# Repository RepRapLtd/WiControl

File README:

Wireless Home/Building Control System
=====================================

Adrian Bowyer
RepRap Ltd
https://reprapltd.com

Licence: GPL

This is a system for controlling devices in buildings (primarily, but not exclusively, heating; it will also do lighting and other things) with a web interface.  It is fully open-source and free.  The licence is the GPL.

There are two versions:

  1. Raspberry Pi + PanStamp in the directory PanStamp. This has been working for a few years, and is now frozen and will not be developed further.

  2. WiFi based on the ESP-8266 in the directory ESP-8266.  This is in development.

Both start with a php script that serves web pages where you can edit, for example, temperature profiles for individual rooms.  That data is saved in files on the server.

The ESP-8266s (or Pi) then get that data and decide(s) what to turn on and off.

More documentation needs to be written...

More importantly, security is minimal and needs to be properly implemented.

See also (for homemade solenoid valves): https://www.thingiverse.com/thing:3496770

WiControl - ESP-8266
====================

This version does everything that the PanStamp version did, but more simply and robustly (the robustness has nothing to do with the hardware change; the PanStamps are fine; it has to do with a simplification of the protocols and hardware).

This version of the system will also support Google Home and Amazon Echo/Alexa.

Some more instructions here would be a good idea...

WiControl - Raspberry Pi + PanStamp
===================================

This allows temperature profiles to be set for each individual room for all times of the day and every day of the week.

It can be controlled using a web browser from anywhere.

It uses Panstamps (http://www.panstamp.com/) for the individual rooms and a Raspberry Pi (https://www.raspberrypi.org/) as the main building controller.

This repository contains all the software and all the hardware designs.

One thing it lacks is full documentation, as I created it for my own use and I know how it works.  Sorry.

Installation:
-------------

On the Pi:

This assumes you have an out-of-the-box Raspberry Pi SD card with no extra software installed.

First set your local timezone:

$ sudo dpkg-reconfigure tzdata

You may want to change the default name of the Pi ("raspberrypi") to something more appropriate 
like "heatingcontrol".  To do that:

$ sudo nano /etc/hostname

That file contains a single name - the name of the Pi.  Change it to what you want, save the file, then reboot.

Change you password:

$ passwd

And enable ssh:

$ sudo raspi-config

Next install Apache and PHP:

$ sudo apt-get update
$ sudo apt-get install apache2 -y
$ sudo apt-get install php5 libapache2-mod-php5 -y

At this point it is a good idea to check that the webserver is now running.  In the URL address bar of a web browser on a PC or phone type

  myname.home/

where myname is the Pi's name that you created above (some networks need myname.local instead).  If you don't get anything type 

$ ifconfig

on the Pi.  This will tell you the Pi's IP address (something like 192.168.1.163).  Type that IP address into the web browser's URL bar.  You should see the default Apache/Debian server homepage.

Next install ftp:

$ sudo apt-get install ftp

And the ftp demon:

$ sudo apt-get install pure-ftpd

Create an ftp user (see https://www.raspberrypi.org/documentation/remote-access/ftp.md) called "upload" with access to the html directory:

$ sudo groupadd ftpgroup
$ sudo useradd ftpuser -g ftpgroup -s /sbin/nologin -d /dev/null
$ pushd /var/www/html/
$ sudo chown -R ftpuser:ftpgroup .
$ sudo pure-pw useradd upload -u ftpuser -g ftpgroup -d /var/www/html -m
[** You will be asked to create a password for the user upload at this point**]
$ sudo pure-pw mkdb
$ sudo ln -s /etc/pure-ftpd/conf/PureDB /etc/pure-ftpd/auth/60puredb
$ sudo service pure-ftpd restart
$ popd

You next need to install the heating software:

$ git clone https://github.com/RepRapLtd/WiControl.git
$ cd WiControl/PanStamp

Copy the control file:

$ cp run-heat-control.sample run-heat-control

and edit the file run-heat-control and replace the "zone-1"s with the name of the zone you want.

Copy the sending file:

$ cp sendtemps.sample sendtemps

and edit the sendtemps file to include the ftp password you set above and to change zone-1 to the name of your zone.

Backup the webserver's index file, and copy all the heating web files there and set permissions:

$ sudo mv /var/www/html/index.html /var/www/html/index.html.old
$ cd Web
$ sudo cp -r * /var/www/html
$ sudo chown -R ftpuser:ftpgroup /var/www/html
$ sudo chmod 666 /var/www/html/*.dat
$ sudo chmod 777 /var/www/html/zone-1-Profiles

Finally

$ sudo crontab -e

and add a line at the end like this:

* * * * * /home/pi/WiControl/run-heat-control

That will cause the shell script run-heat-control to be run once a minute.

On the PanStamps:

You can just about run the Arduino IDE on the Raspberry Pi, but it's probably better to
use a big serious computer to do this bit.  Install the Arduino IDE on your computer if
you haven't already got it:

https://www.arduino.cc/en/Main/Software

And clone the repository https://github.com/RepRapLtd/WiControl.git as you did on the Pi.

Load the arduino program in the folder Panstamp-control into the IDE.

At the head of the file Control.h set up your heating zones and device names and numbers.  Load 
this program into each device (e.g. boiler, radiator) on your heating system.

Running
-------

When it runs it creates a status file called Status.

$ cat Status

will tell you what your system last did.  If you

$ touch Log

then each time run-heat-control runs it will append the status
report to the end of itself, which keeps a history and is therefore
useful for debugging.

When you have finished debugging don't forget to

$ rm Log

otherwise it will eventually fill up the SD/disc...

Adrian Bowyer

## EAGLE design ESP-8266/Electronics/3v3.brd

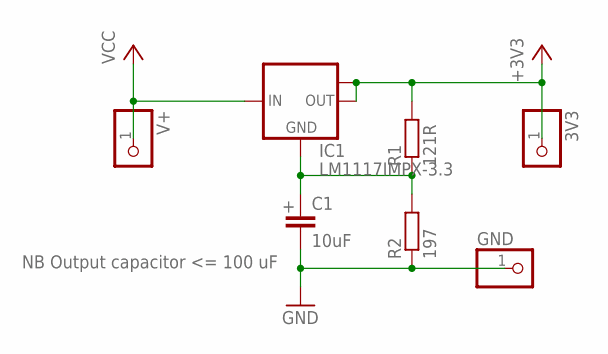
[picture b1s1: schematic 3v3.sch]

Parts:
3V3: PINHD-1X1; 1X01
C1: 10uF; C0805
GND: PINHD-1X1; 1X01
IC1: LM1117IMPX-3.3; SOT223
R1: 121R; M0805
R2: 197; M0805
V+: PINHD-1X1; 1X01

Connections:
+3V3: 3V3.1, IC1.2 (OUT), IC1.TAB (OUT1), R1.2
GND: C1.2, GND.1, R2.1
unnamed: C1.1, IC1.1 (GND), R1.1, R2.2
VCC: IC1.3 (IN), V+.1

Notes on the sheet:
NB Output capacitor <= 100 uF

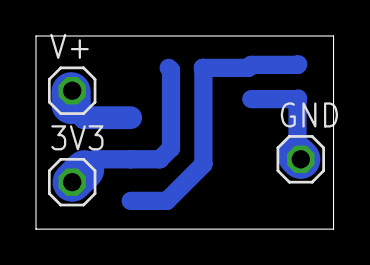
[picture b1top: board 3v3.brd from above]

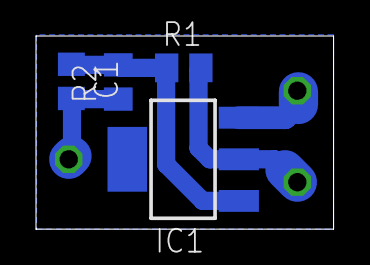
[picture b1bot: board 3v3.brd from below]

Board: 2 copper layers, 16.5 x 10.7 mm, 7 parts (4 on the bottom side), 4 nets.

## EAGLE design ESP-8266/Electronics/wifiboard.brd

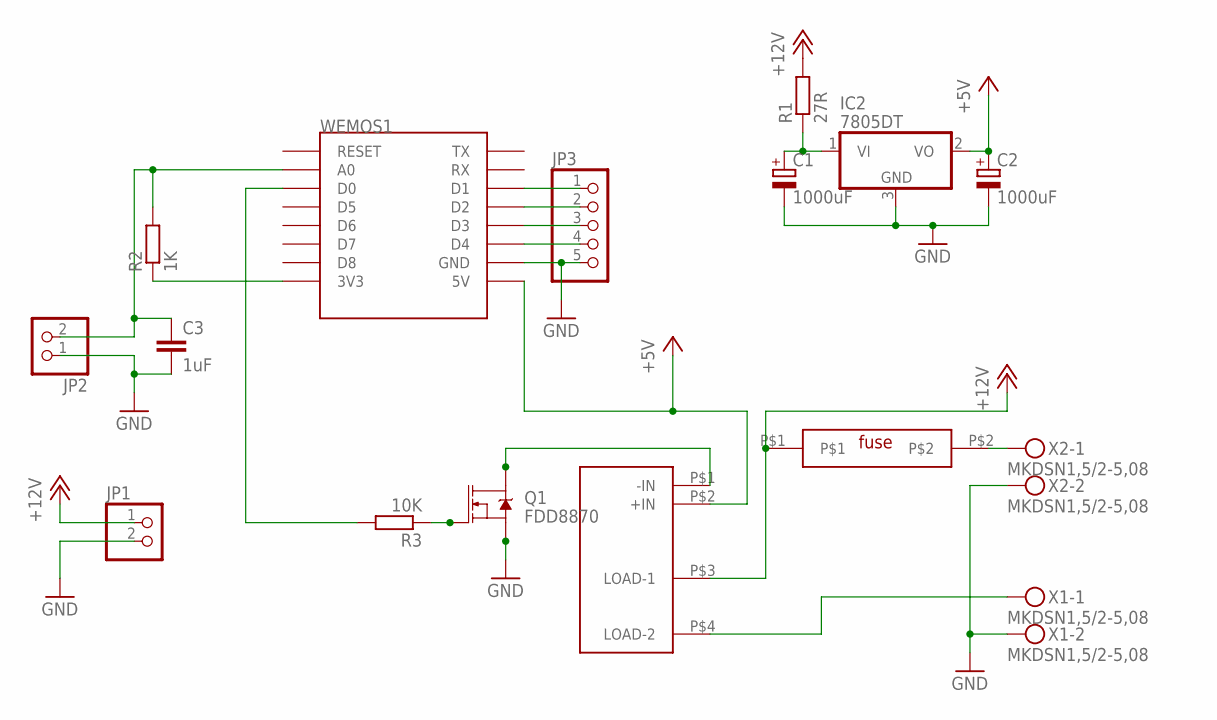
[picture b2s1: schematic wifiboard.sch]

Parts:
C1, C2: 1000uF; B45181B
C3: 1uF; C0805
IC2: 7805DT; TO252
JP1, JP2: PINHD-1X2; 1X02
JP3: PINHD-1X5; 1X05
Q1: FDD8870; DPAK
R1: 27R; 0207/10
R2: 1K; M0805
R3: 10K; M0805
U$1: OMRON-G6DS; OMRON-G6DS-1A-H
U$2: FUSE
WEMOS1: WEMOS-D1-MINI
X1, X2: MKDSN1,5/2-5,08

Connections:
+5V: C2.+, IC2.2 (VO), U$1.P$2 (+IN), WEMOS1.5V
+12V: JP1.1, R1.2, U$1.P$3 (LOAD-1), U$2.P$1
GND: C1.-, C2.-, C3.2, IC2.3 (GND), JP1.2, JP2.1, JP3.5, Q1.3 (S), WEMOS1.GND, X1.2, X2.2
unnamed: C1.+, IC2.1 (VI), R1.1
unnamed: C3.1, JP2.2, R2.2, WEMOS1.A0
unnamed: R2.1, WEMOS1.3V3
unnamed: Q1.1 (G), R3.1
unnamed: R3.2, WEMOS1.D0
unnamed: Q1.4 (D), U$1.P$1 (-IN)
unnamed: U$1.P$4 (LOAD-2), X1.1
unnamed: JP3.4, WEMOS1.D4
unnamed: U$2.P$2, X2.1
unnamed: JP3.3, WEMOS1.D3
unnamed: JP3.2, WEMOS1.D2
unnamed: JP3.1, WEMOS1.D1

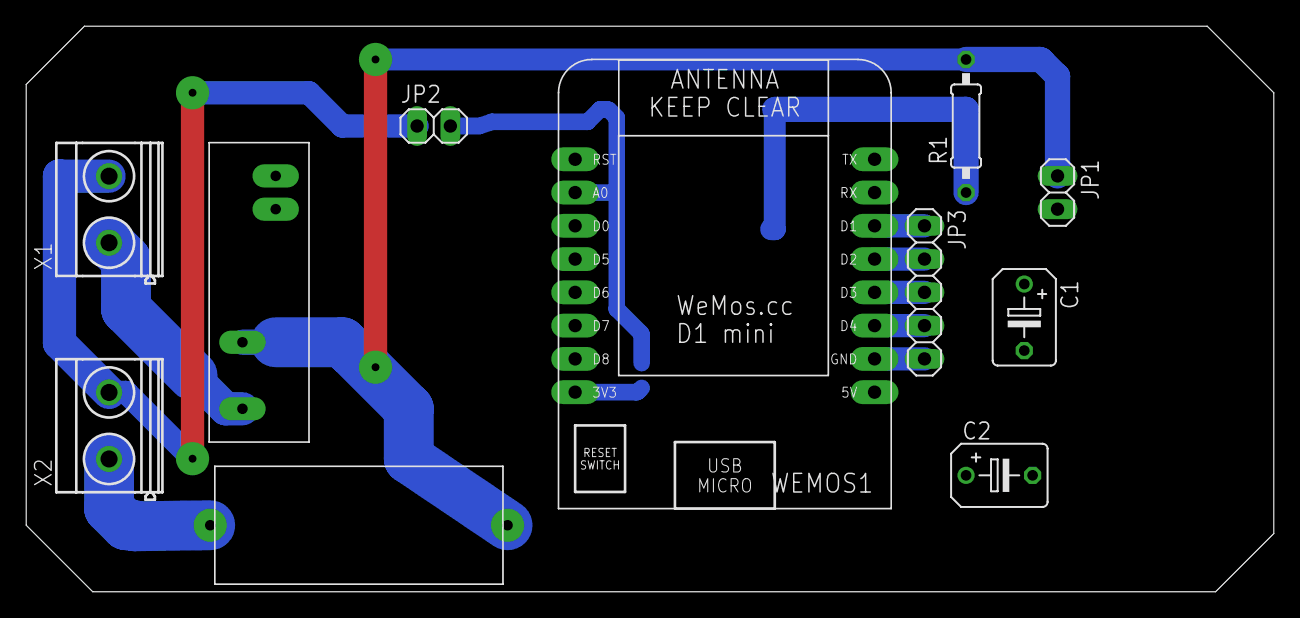
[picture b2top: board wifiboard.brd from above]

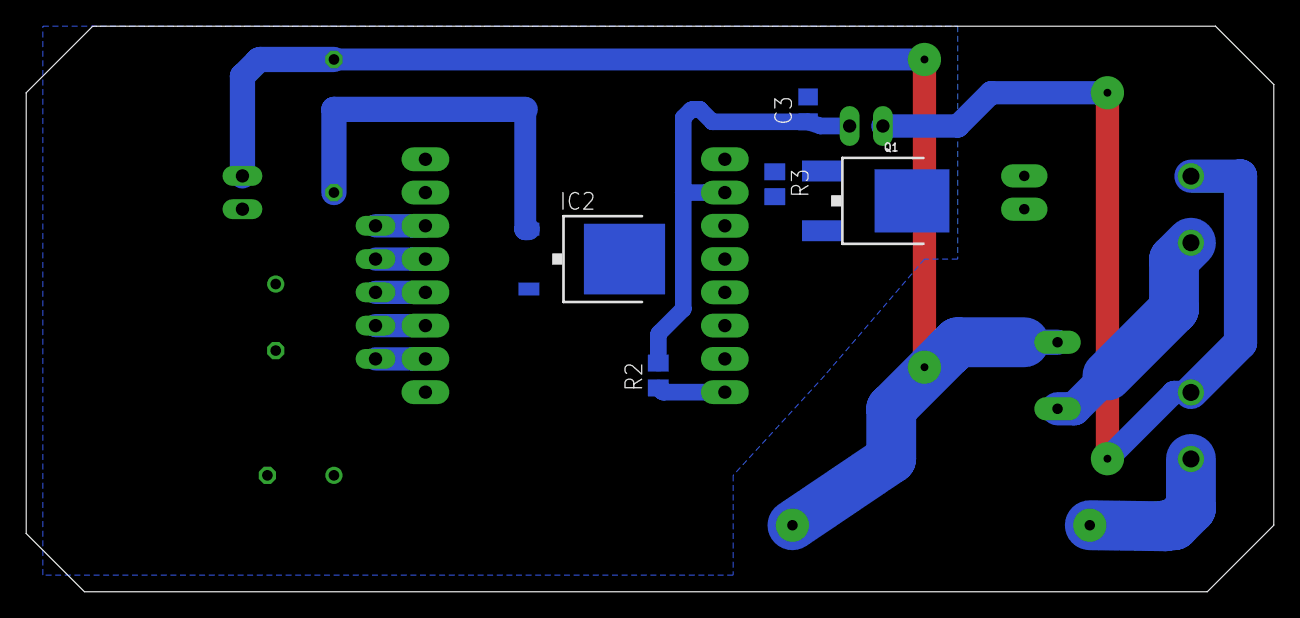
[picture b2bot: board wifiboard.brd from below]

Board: 2 copper layers, 95.2 x 43.2 mm, 16 parts (5 on the bottom side), 15 nets.

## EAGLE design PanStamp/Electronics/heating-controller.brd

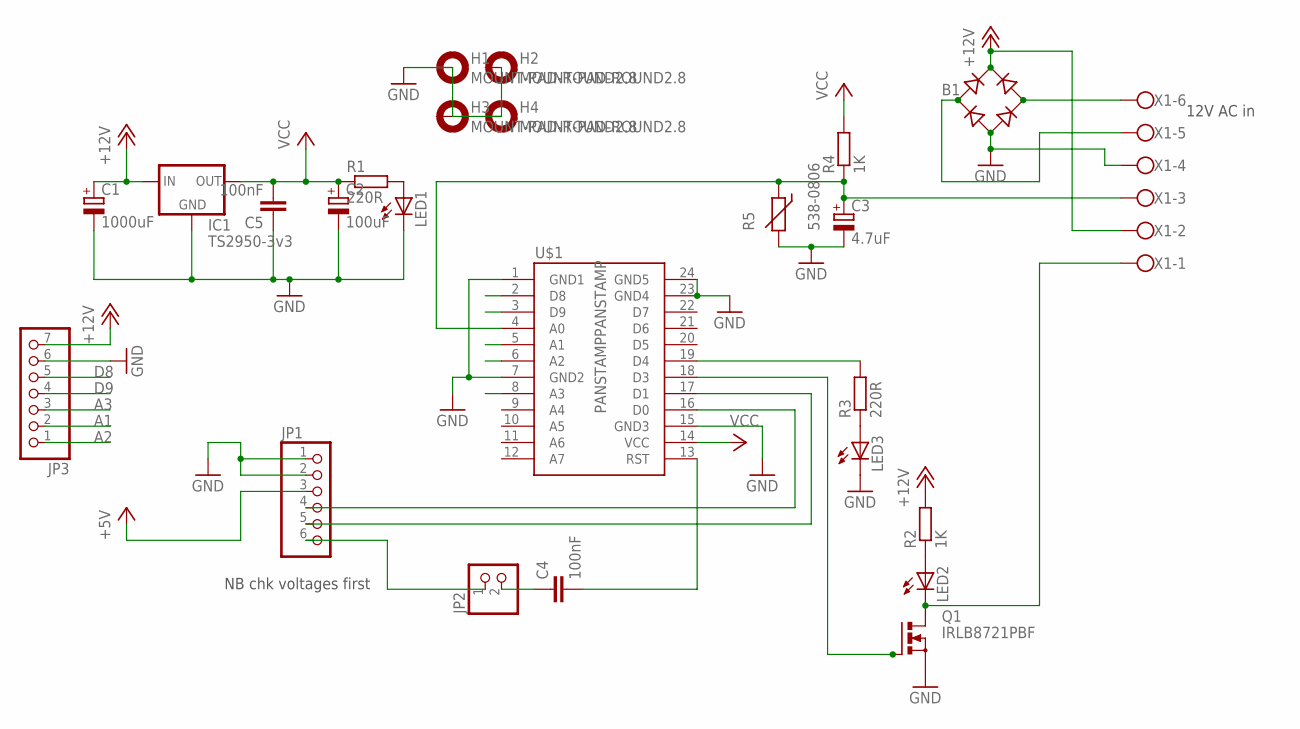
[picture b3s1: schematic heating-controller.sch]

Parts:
B1: B-DIL
C1: 1000uF; E3,5-10
C2: 100uF; E3,5-10
C3: 4.7uF; E3,5-10
C4, C5: 100nF; C050-024X044
H1, H2, H3, H4: MOUNT-PAD-ROUND2.8; 2,8-PAD
IC1: TS2950-3v3; TO92
JP1: PINHD-1X6; 1X06
JP2: PINHD-1X2; 1X02
JP3: PINHD-1X7; 1X07
LED1, LED2, LED3: LED3MM
Q1: IRLB8721PBF; TO220BV
R1, R3: 220R; 0207/7
R2, R4: 1K; 0207/7
R5: 538-0806; RS-2,5
U$1: PANSTAMPPANSTAMP; DIL24-6
X1: W237-6

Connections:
+5V: JP1.3
+12V: B1.+, C1.+, IC1.3 (IN), JP3.7, R2.2, X1.2
A1: JP3.2, U$1.5 (A1)
A2: JP3.1, U$1.6 (A2)
A3: JP3.3, U$1.8 (A3)
D8: JP3.5, U$1.2 (D8)
D9: JP3.4, U$1.3 (D9)
GND: B1.-, C1.-, C2.-, C3.-, C5.1, IC1.2 (GND), JP1.1, JP1.2, JP3.6, LED1.K (C), LED3.K (C), Q1.S, R5.2, U$1.1 (GND1), U$1.7 (GND2), U$1.15 (GND3), U$1.23 (GND4), U$1.24 (GND5), X1.4
unnamed: C3.+, R4.1, R5.1, U$1.4 (A0), X1.3
unnamed: R3.2, U$1.19 (D4)
unnamed: LED2.K (C), Q1.D, X1.1
unnamed: LED1.A, R1.2
unnamed: LED2.A, R2.1
unnamed: LED3.A, R3.1
unnamed: Q1.G, U$1.18 (D3)
unnamed: C4.1, JP2.2
unnamed: JP1.4, U$1.16 (D0)
unnamed: JP1.5, U$1.17 (D1)
unnamed: B1.AC1, X1.6
unnamed: JP1.6, JP2.1
unnamed: B1.AC2, X1.5
unnamed: C4.2, U$1.13 (RST)
VCC: C2.+, C5.2, IC1.1 (OUT), R1.1, R4.2, U$1.14 (VCC)

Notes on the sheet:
NB chk voltages first
12V AC in

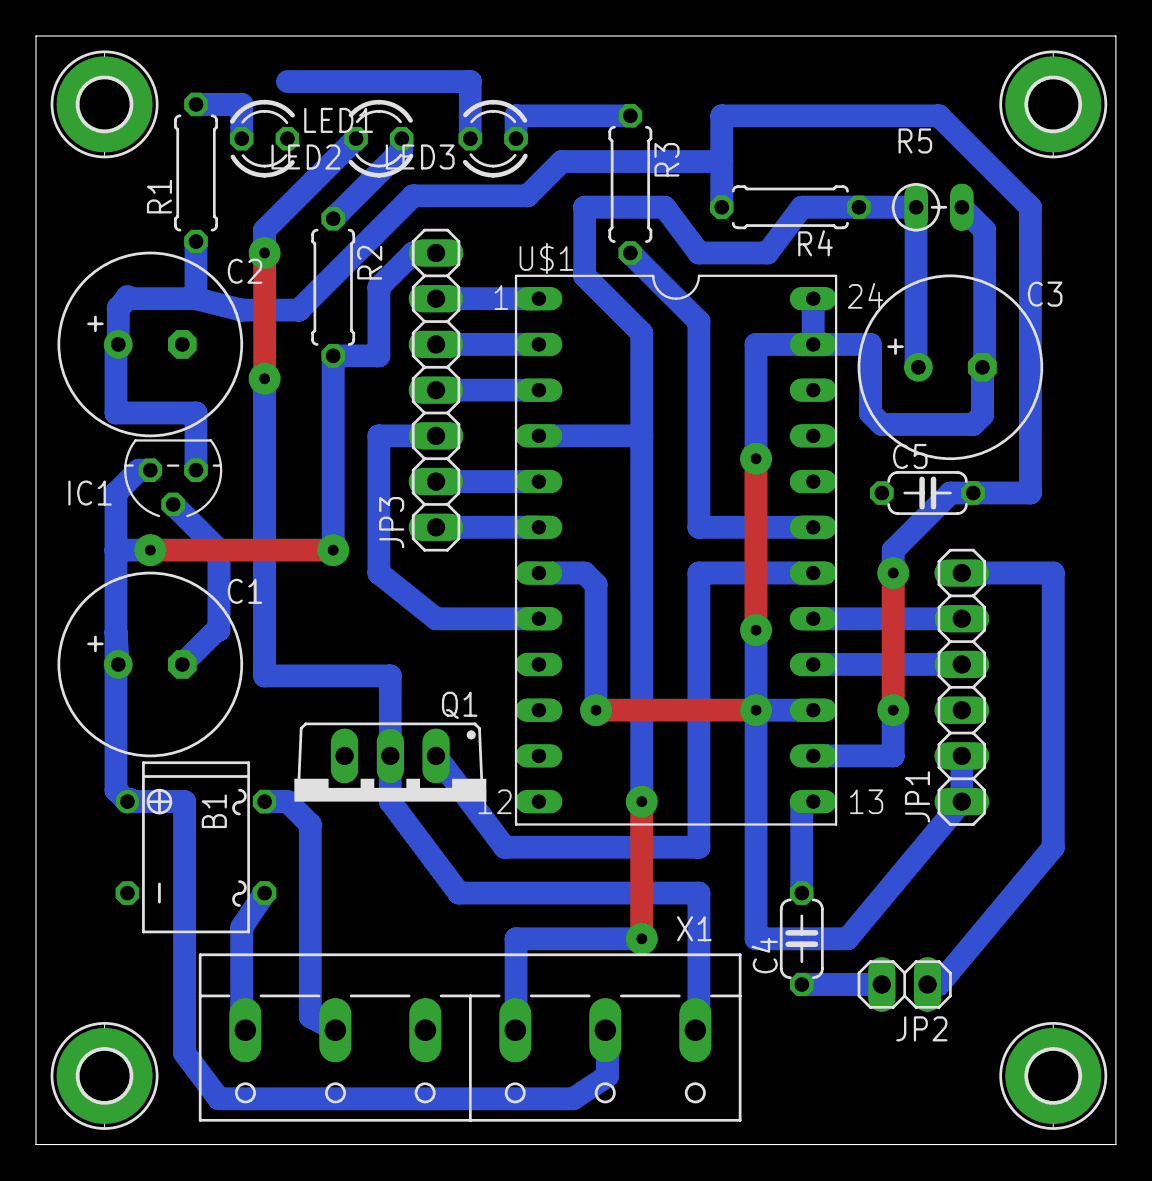
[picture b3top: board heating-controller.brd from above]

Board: 2 copper layers, 60.0 x 61.6 mm, 25 parts (0 on the bottom side), 22 nets.

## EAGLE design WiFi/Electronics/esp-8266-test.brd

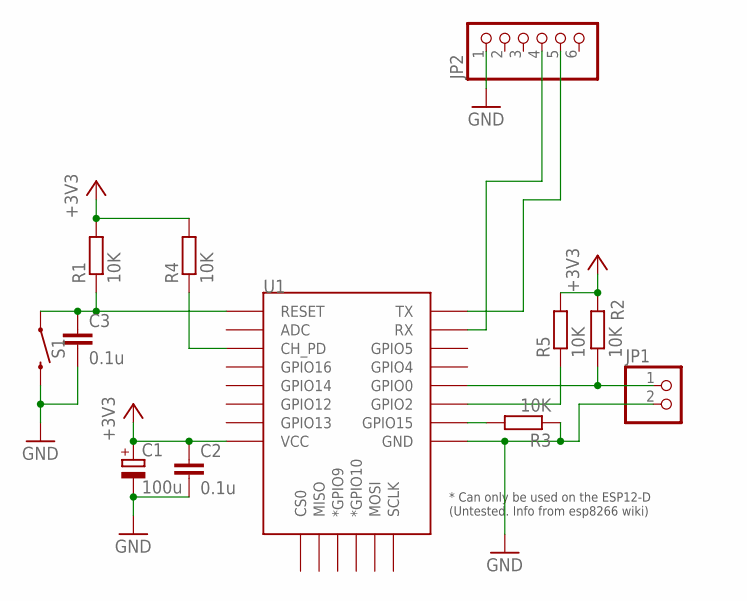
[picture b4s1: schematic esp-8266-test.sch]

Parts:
C1: 100u; 085CS_1AR
C2, C3: 0.1u; C0805
JP1: PINHD-1X2; 1X02
JP2: PINHD-1X6; 1X06
R1, R2, R3, R4, R5: 10K; R0805
S1: TACTILE_SWITCH_SMD_4.6X2.8MM
U1: ESP12ESMD; ESP12E-SMD

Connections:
+3V3: C1.+, C2.1, R1.2, R2.2, R4.2, R5.2, U1.VCC
GND: C1.-, C2.2, C3.2, JP1.2, JP2.1, R3.1, S1.3 (2), S1.4 (2), U1.GND
unnamed: C3.1, R1.1, S1.1, S1.2 (1), U1.RESET
unnamed: JP1.1, R2.1, U1.GPIO0
unnamed: JP2.4, U1.RXD0 (RX)
unnamed: R3.2, U1.GPIO15
unnamed: JP2.5, U1.TXD0 (TX)
unnamed: R4.1, U1.CH_PD
unnamed: R5.1, U1.GPIO2

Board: 2 copper layers, 12 parts (0 on the bottom side), 9 nets, no tracks yet.

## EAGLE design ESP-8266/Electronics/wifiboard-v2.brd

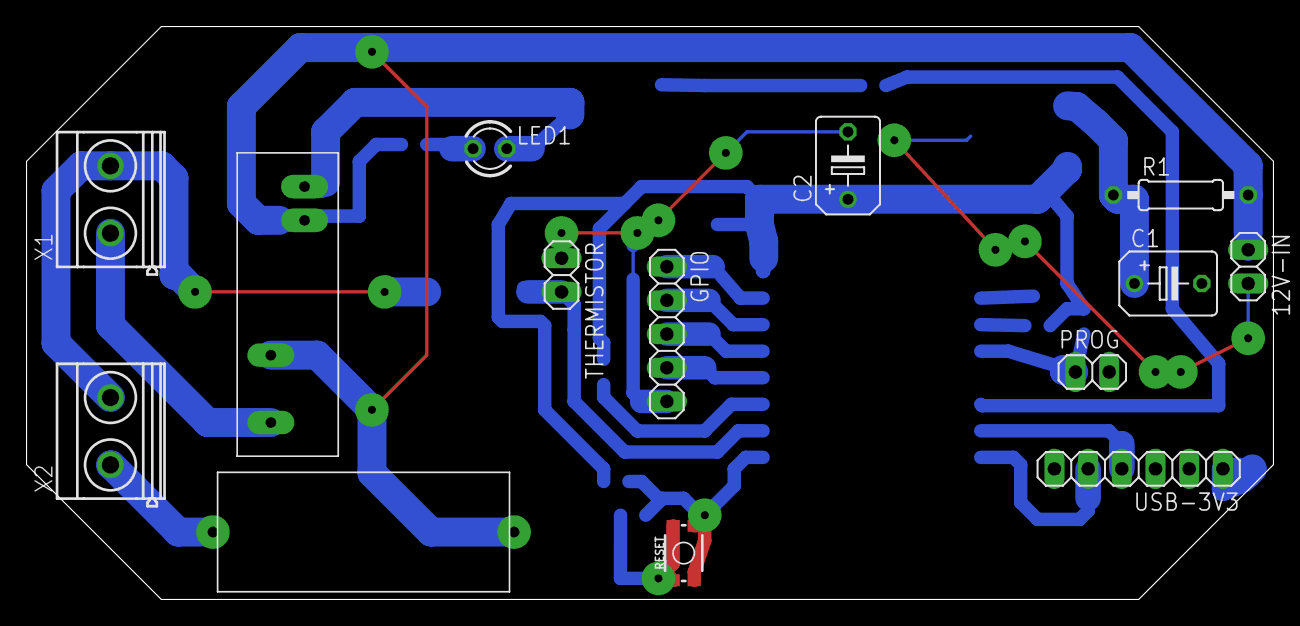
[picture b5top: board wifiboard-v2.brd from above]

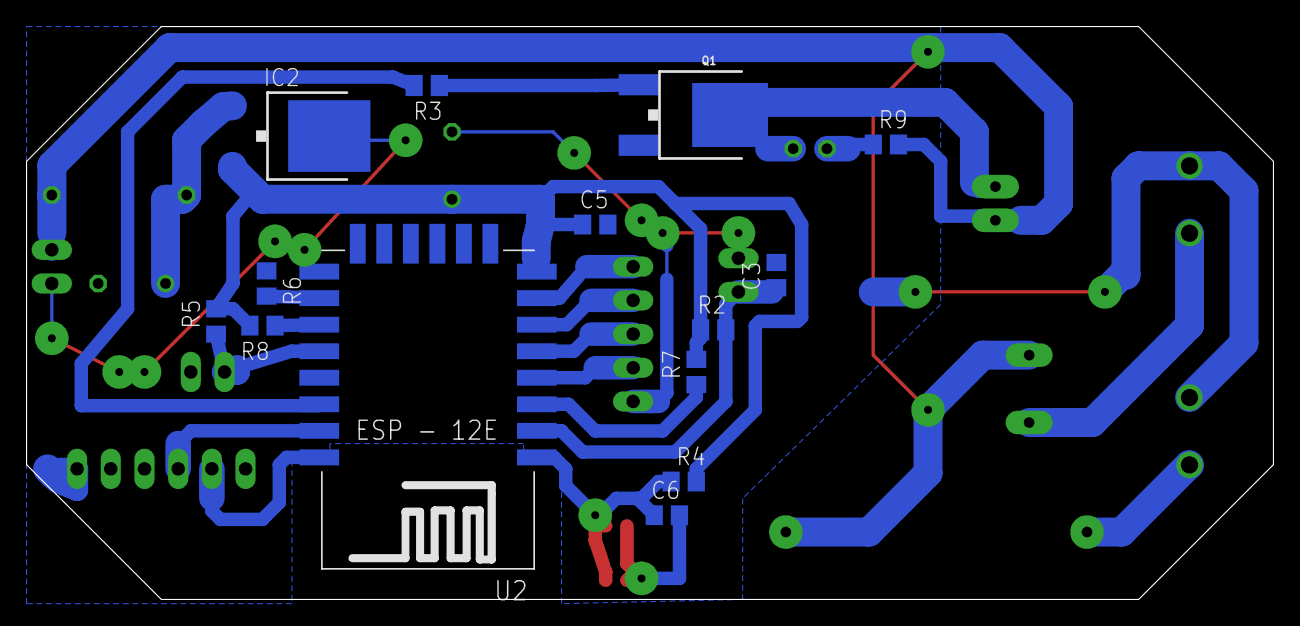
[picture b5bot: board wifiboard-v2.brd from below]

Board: 2 copper layers, 94.0 x 43.2 mm, 28 parts (14 on the bottom side), 22 nets.

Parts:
12V-IN: 1X02
C1, C2: 1000uF; B45181B
C3: 1uF; C0805
C5, C6: 0.1u; C0805
FUSE: FUSE
GPIO: 1X05
IC2: 78033AF; TO252
LED1: LED3MM
PROG: 1X02
Q1: FDD8870; DPAK
R1: 6R8; 0207/10
R2, R3: 10K; M0805
R4, R5, R6, R7, R8: 10K; R0805
R9: 1K; R0805
RELAY: OMRON-G6DS; OMRON-G6DS-1A-H
RESET: TACTILE_SWITCH_SMD_4.6X2.8MM
THERMISTOR: 1X02
U2: ESP12E-SMD
USB-3V3: 1X06
X1: AC-N; MKDSN1,5/2-5,08
X2: AC-L; MKDSN1,5/2-5,08

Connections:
0: PROG.1, R5.1, U2.GPIO0
2: R8.1, U2.GPIO2
5: R3.2, U2.GPIO5
12: GPIO.2, U2.GPIO12
13: GPIO.1, U2.GPIO13
14: GPIO.3, U2.GPIO14
15: R6.2, U2.GPIO15
16: GPIO.4, U2.GPIO16
+3V3: C2.+, C5.1, IC2.2, R2.1, R4.2, R5.2, R7.2, R8.2, U2.VCC
+12V: 12V-IN.1, FUSE.P$1, R1.2, R9.2, RELAY.P$2, RELAY.P$3
A0: C3.1, R2.2, THERMISTOR.2, U2.ADC
CH_PD: R7.1, U2.CH_PD
GND: 12V-IN.2, C1.-, C2.-, C3.2, C5.2, C6.2, GPIO.5, IC2.3, PROG.2, Q1.3, R6.1, RESET.3, RESET.4, THERMISTOR.1, U2.GND, USB-3V3.1, X1.2, X2.2
unnamed: C1.+, IC2.1, R1.1
unnamed: Q1.1, R3.1
unnamed: LED1.K, Q1.4, RELAY.P$1
unnamed: RELAY.P$4, X1.1
unnamed: FUSE.P$2, X2.1
unnamed: LED1.A, R9.1
RST: C6.1, R4.1, RESET.1, RESET.2, U2.RESET
RX: U2.RXD0, USB-3V3.4
TX: U2.TXD0, USB-3V3.5

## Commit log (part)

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2013-10-27 Panstamp wireless control system - first commit.
2013-10-29 Minor tidying.
2013-11-02 Simple command interpreter added.
2013-11-04 Adding more commands...
2013-11-06 Bug: received message never acted on...
2013-11-08 First working version.
2013-11-15 Thermistor parameters corrected.
2013-11-17 Sketch of controller PCB started in Eagle.
2013-11-17 First version of PCB complete.
2013-11-17 Final (?) PCB design.
2013-11-17 Tidied final (?) PCB design.
2013-11-19 Extras added to PCB, + tidying.
2013-11-19 More tidying...
2013-12-07 Smaller 3v3 reg used, that can also stand 20V.
2013-12-19 Added Gerber files.
2014-01-04 First test of PCB. It works!
2014-01-07 BoM spreadsheeet added.
2014-01-07 Case design added.
2014-01-11 Code tidying.
2014-01-14 Starting work on the Host software.
2014-01-14 More work on the Host software.
2014-01-15 More host s/w...
2014-01-16 More host s/w
2014-01-18 First working version of the host control software.
2014-01-18 Minor improvements to output from host.
2014-01-20 Now with retries.
2014-01-30 Watchdog reset added at 30 secs. Timer is reset if a radio message arrives.
2014-01-31 Watchdog timer added.
2014-02-01 Tidying...
2014-02-06 usleep(2000) added to wait for incoming USB bytes on the host s/w so it doesn't hog CPU cycles in a tight loop waiting for bytes (which will be buffered anyway).
2014-05-12 Test trivial modification
2014-06-14 Added code to invert temperature behaviour to allow the control of cooling devices. Added code to allow the sensor Panstamp number to be different from the switch Panstamp number. Temperature profile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
2014-06-14 First version of the web interface PHP written.
2014-07-27 Case design improved and made partly parametric.
2014-07-29 Timeout on wget added.
2014-07-29 Raspberry Pi Version
2014-07-31 Libserial for R Pi added. Presence of Log file is now used to decide whether to append to it or to throw the output away.
2014-08-19 RGB LED lighting control added.
2014-08-24 U floor added.
2014-08-24 Proper delay timing added.
2014-08-25 Named location added to each Panstamp.
2014-08-25 Heating control program now allows multiple devices per room and temperature.
2014-08-25 String limit changed to *. All seems to work...
2014-08-25 Firmware built with make outside Eclipse.
2014-08-25 Final ??? Version...
2014-08-28 Control now configured for latest Eclipse Arduino and arduino-1.5.7
2014-08-28 Fixed libserial for the pi.
2014-08-31 Host code tidying - Device class used throughout. Delays added in poll loops.
2014-09-13 Starting to fit in the main house...
2014-09-13 Gradual LED fade added.
2014-09-26 Heatprofile bug squashed (deviceCount too big).
2014-09-26 This time with the correct run_heat_control...
2014-10-07 STatus and Log implemented.
2014-10-12 Time and date commands added to control firmware.
2014-10-12 On/Off switching made more robust.
2014-10-12 Added time setting to host software.
2014-10-12 Ignore updated to remove shell script from commits
2014-10-12 Sample shell script added.
2014-10-12 Now prints the time from the Panstamp.
2014-10-12 Now with daylight saving...
2014-10-12 Correct printf format now used for sending unsigned long time...
2014-10-17 Added link to pi ntp stuff.
2014-10-18 File tidying plus better README.md file.
2015-01-16 Good settings for A&C saved.
2015-02-08 Proper web interface... WIP
2015-02-08 Example shell script...
2015-02-14 New Webform just about complete
2015-02-15 need to sudo apt-get install gettext
2015-02-22 Shellscript amended to put absolute path for wget in.
2015-02-22 Removed unwanted files
2015-02-22 Removed unwanted files.
2015-03-01 Temperature log file upgraded to have set temps in as well as room temps, and a heating on/off flag.
2015-03-26 Getting Eclipse compiling the Panstamp program again...
2015-08-28 README file improved...
2015-08-28 README made more legible
2015-08-28 Again readability...
2015-08-28 Readability
2015-08-29 Further README corrections
2015-09-01 Fixed problem with wput compilation
2015-09-20 Host now reads the old temperature profile and uses those temps if wireless to a device fails.
2015-10-02 Script updated to record stderr as well as stdout.
2015-10-15 Reverting to adrianbowyer.net
2016-01-17 Bug in Switch class fixed.
2016-01-31 Improving Panstamp debugging. WIP.
2016-03-15 Fixed -10 temp bug
2016-03-15 Pi version
2016-03-15 removed surplus
2016-07-28 Bringing in-line with latest version
2016-07-28 Fixed temperature rounding and transmission as 10* int.
2016-07-28 Fixed (I think) watchdog.
2016-07-28 Fixed README
2016-07-29 Setting up classic Makefile for Pi-control
2016-07-30 New working version of Pi host program.
2016-07-31 Changed output to make Log more readable when ther is a timeout.
2016-07-31 This time with correct logic...
2016-07-31 Added code to check for non-responding devices.
2016-07-31 Minor tidying
2016-09-12 Fixed dud start of winter (month 8!).
2016-11-03 Updated README and added .gitignore (not before time...).
2016-11-03 Removed edit backup files.
2016-11-03 More README...
2016-11-03 File tidying and adding latest server side web code.
2016-11-03 Added code to run server side on local server.
2016-11-04 Full local control now working
2016-11-04 Combining server and controller on the same Pi.
2016-11-06 Finalising and tidying local server version. Updating README.
2016-11-06 Further tidying...
2017-01-31 More README updating
2017-02-05 Started work on Networked/WiFi replacement for PanStamps.
2017-06-05 WeMos design added. Not final (need to replace 78L05 with 7805 to get enough current).
2017-11-14 Working on the WiFi/ESP-8266 version...
2017-12-04 Tidied up wifi files. Added WiFi FreeCAD case.
2017-12-07 Improved PCB design and casing.
2017-12-29 Started work on the WiFi client for the domestic control system.
2017-12-31 WIP - WiFi controller
2018-01-01 First version of the ESP8266 software.
2018-01-02 More work on the s/w...
2018-01-03 Nearly finished the server .php script
2018-01-04 First working (?) version of the WiFi controller php program.
2018-01-05 Debugging the WiFi PHP script.
2018-01-08 Improved .PHP control program
2018-02-09 Finalising (?) the ESP-8266 code and the .php script.
2018-02-15 Remote server working. Backup server added to Arduino code (doesn't yet work...)
2018-02-21 Minor improvements to debugging behaviour.
2018-03-15 heating.php improved to check that times monotonically increase throughout the day.
    Various bits of experimental WiFi electronics added.
2018-03-16 More correctness checking in heating.php
2018-04-12 Simple web monitoring added to the thermostat program.
2018-04-13 Improvements to thermostat
2018-04-17 Tidying ControlNode for the WiFi heating system.
2018-05-01 controllednode.php fixed to deal with timezone (maybe summer time too?)
2018-05-01 This time with the right filename...
2018-05-03 Improving the box design. Also fixed daylight saving in controllednode.php
2018-07-17 Gerbers for WiFi PCB done.
2018-07-18 WiFi PCB as ordered.
2018-09-04 Test changes; none significant.
2018-09-05 New version of the WiFi client end firmware written, ControlledNode2. Seems to work...
2018-09-06 Parts spreadsheet set up. PHP changed to make summertime work.
2018-09-07 Improved case design.
2018-09-07 More robust version of post.php
2018-09-07 Controlnode programs (these need new names...) modified to set and use the switching delays.
2018-09-10 Adding multiple loads to the control firmware. W.I.P.
2018-09-10 Load class in WiFi firmware now compiles. More W.I.P.
2018-09-10 Multi-device controlling firmware works...
2018-09-11 ESP8266-12 pinouts added to HomeControlFirmware.h
2018-09-12 Improved README...
2018-09-12 File tidying.
2018-09-12 Now with the right names...
2018-09-12 Increasing the number of mains adapters that can be incorporated.
2018-09-18 New power-supply case added. Tidied file structure. More comments in software.
2018-09-25 Set temp offset to 0. Added complete parts list.
2018-11-07 Firmware now reports internal status, and connecting to WiFi.
2018-11-07 More TODOs added.
2018-11-08 .php script improved to detect and report dead devices.
2018-11-29 WIP: Adding a class to record and recover strings from flash memory so that the device can be configured on the fly and remember that when it's powered off then on again.
2018-11-29 Sm. bug spotted and fixed.
2018-11-30 Saving and loading settings to/from flash (seems to be) working.
2018-12-02 Fully flash-configurable version of the client firmware.
2018-12-12 Client prompt early in boot.
2018-12-13 Temperature offset added to the configurable variables.
2019-01-11 Added image of schematic
2019-01-23 WiFi works. Horay!
2019-01-30 File reorganising
2019-02-26 New branch.
    Started work on Sally's idea of having each client just identified by a number,
    along with a table on the server that matches numbers to locations.
    New client ESP8266 code compiles...
2019-02-28 First full working version of Sally's idea.
2019-03-04 Data logging added to the new system.
2019-03-09 Improved lid design with connector.
2019-07-01 Small bug in scontrollednode.php fixed.
2019-08-15 Added file-touch .php script heatsource.php to allow the old system to turn on a boiler in the new system.
2019-08-15 Added short bit to shell script to turn boiler in the new system on from the old system.
2019-09-24 Sorted out update of globals.php
2019-09-25 Fixed small bug in the .php script; updated URLs for home system.
2019-09-25 Added example HTTP request in comment
2019-10-02 Better globals.php...
2019-10-02 Shell script added to test if new system has requested the boiler to be on and to relay that to the master server.
2019-10-03 Updated units.dat
2019-10-03 Multi controller for underfloor added to units
2019-10-04 Tidied Client software.
2019-10-04 Tidying HomeControlFirmware.h
2019-10-18 Fixing (ish) problem with multiple loads. Can't seem to have more than 3, though there's 50K of heap. ???
2019-10-26 Retained crimp plug for valve connection added to design.
2019-11-14 Fixing transparency, but there seems to be a bug in the screw corner retainers...
2019-11-14 Fixed fault in walls design. Salvaged from previous commit.
2019-11-19 scontrollednode.php improved - CSV logfile generation added; more sensible time and date formats in output.
2019-11-19 Updating globals.php
2019-11-30 Removing error exits and putting messages in debug string.
2019-11-30 Updated template for local wifi .H file
2019-11-30 Removed error exits from scontrollednode.php and replaced with reporting error string.
2019-11-30 error string added to globals.
2019-11-30 Turning logging on and getting the log from the web interface W.I.P.
2019-12-01 Web control of data logging implemented.
2020-04-25 Added link to 3D printed motorised valve.
2020-05-11 Updated php script because of !*$**!! depricated message suddenly introduced
2020-09-29 Deprecated usages of parse_str removed from PHP files.
2020-10-19 Added code to output Unix times into the logs.
2020-12-06 Set off temperature from 10C to 5C in scontrollnode.php
2021-02-26 Keeping repo up to date with online version.
2021-04-27 Sally's WIP on new PCB design.
2021-05-06 Tidying files; previous...
2021-06-18 Now saves configuration in EEPROM (if it works...)
2021-06-18 Debugging WIP...
2021-06-21 Updated firmware with interactive setup.
2021-07-10 Updated deprecated wifi code.
2021-07-11 Added erase flash option on boot in debug mode.
2022-01-11 Added hysterisis to the system's ON/OFF with temperature.
2022-01-12 Correcting units.dat
2022-01-28 Trying to start V4 PCB. Not working yet.
2022-01-31 Redoing V4 electronics to make it fully KiCAD.
2022-02-01 V4 schematic complete (?)...
2022-02-02 Components positioned on PCB.
2022-02-03 SB & AB PCB layout
2022-02-09 PCB sent for trial production.
2022-02-14 Double patress box front plate design first complete design.
2022-02-15 Improved patress front plate design.
2022-02-21 This time with the right size for the PCB...
2022-05-20 Keeping things up to date.
2022-07-06 PCB modified to accommodate relay as well as opto-SCR. GERBERS need to be updated.
2024-05-03 Added stuff on hacking existing smart switches, specifically SWA1.
2024-05-03 Comments updated.
2024-05-03 More comments
2024-05-03 cpmments...

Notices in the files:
parts and their libraries:
SparkFun-DiscreteSemi: Licensing: Creative Commons ShareAlike 4.0 International - https://creativecommons.org/licenses/by-sa/4.0
